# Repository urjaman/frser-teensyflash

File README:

Firmware for serprog on a Teensy 3.1,
supports my hardware (see hardware/)
with LPC,FWH and SPI.

You'll need to modify the Makefile
to point to your teensy toolchain,
assumed to be still inside
arduino 1.6.5.

It might be possible to still
compile under cygwin on windows,
but this was only tested on linux.

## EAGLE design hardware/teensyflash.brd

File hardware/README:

There be the EAGLE files (.sch,.brd) here,
gerbers in the .zip.
And the board is also shared in oshpark:
https://oshpark.com/shared_projects/izukIxq8

It is actually a bit tricky to build,
but i managed it. Dont short the PLCC
pins to the pin holes and dont
push the pins through the holes,
just in the holes, because the PLCC
socket goes above them.

There's a more detailed assembly description at:
http://flashrom.org/Teensy_3.1_SPI_%2B_LPC/FWH_Flasher

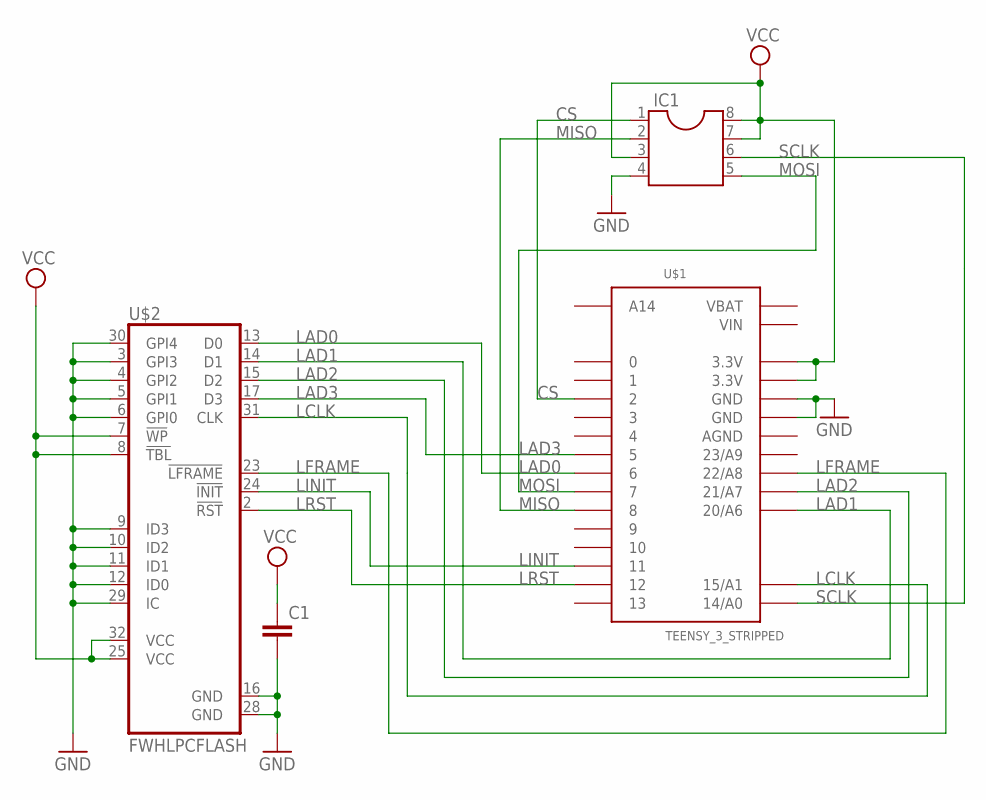
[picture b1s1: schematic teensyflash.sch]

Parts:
C1: C-EUC0805; C0805
IC1: DIL8; DIL08
U$1: TEENSY_3_STRIPPED
U$2: FWHLPCFLASH; PLCC32

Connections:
AGND: U$1.AGND
CS: IC1.1, U$1.2
GND: C1.2, IC1.4, U$1.GND, U$1.GND1 (GND), U$2.3 (GPI3), U$2.4 (GPI2), U$2.5 (GPI1), U$2.6 (GPI0), U$2.9 (ID3), U$2.10 (ID2), U$2.11 (ID1), U$2.12 (ID0), U$2.16 (GND), U$2.28 (GND), U$2.29 (IC), U$2.30 (GPI4)
LAD0: U$1.6, U$2.13 (D0)
LAD1: U$1.20/A6, U$2.14 (D1)
LAD2: U$1.21/A7, U$2.15 (D2)
LAD3: U$1.5, U$2.17 (D3)
LCLK: U$1.15/A1, U$2.31 (CLK)
LFRAME: U$1.22/A8, U$2.23 (!LFRAME)
LINIT: U$1.11, U$2.24 (!INIT)
LRST: U$1.12, U$2.2 (!RST)
MISO: IC1.2, U$1.8
MOSI: IC1.5, U$1.7
SCLK: IC1.6, U$1.14/A0
VBAT: U$1.VBAT
VCC: C1.1, IC1.3, IC1.7, IC1.8, U$1.3.3V, U$1.3.3V1 (3.3V), U$2.7 (!WP), U$2.8 (!TBL), U$2.25 (VCC), U$2.32 (VCC)
VIN: U$1.VIN

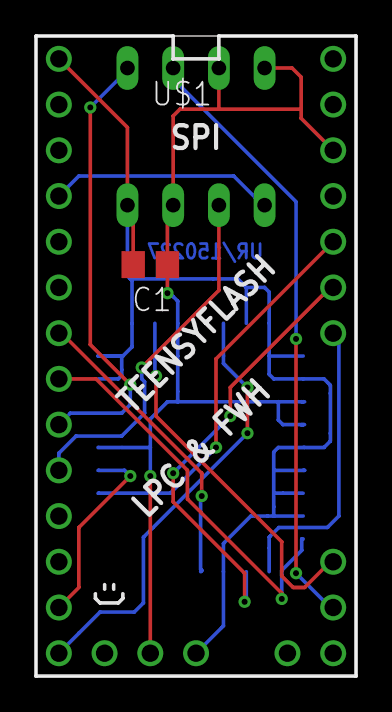
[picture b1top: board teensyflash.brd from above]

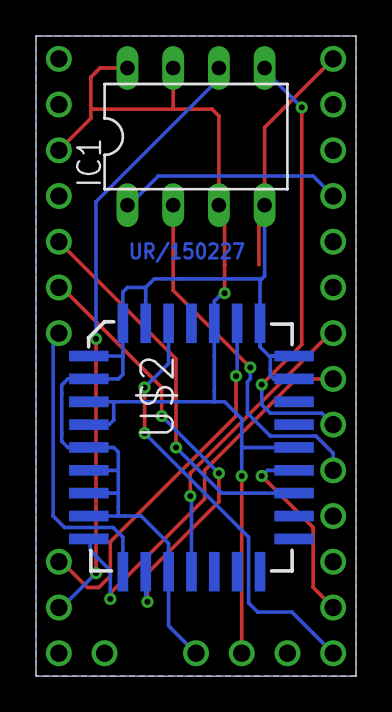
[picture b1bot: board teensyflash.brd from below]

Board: 2 copper layers, 17.8 x 35.6 mm, 4 parts (2 on the bottom side), 14 nets.

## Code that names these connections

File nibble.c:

/*
	This file was part of bbflash, now frser-teensyflash.
	Copyright (C) 2013, Hao Liu and Robert L. Thompson
	Copyright (C) 2013,2015 Urja Rannikko <urjaman@gmail.com>

	This program is free software: you can redistribute it and/or modify
	it under the terms of the GNU General Public License as published by
	the Free Software Foundation, either version 3 of the License, or
	(at your option) any later version.

	This program is distributed in the hope that it will be useful,
	but WITHOUT ANY WARRANTY; without even the implied warranty of
	MERCHANTABILITY or FITNESS FOR A PARTICULAR PURPOSE.  See the
	GNU General Public License for more details.

	You should have received a copy of the GNU General Public License
	along with this program.  If not, see <http://www.gnu.org/licenses/>.
*/
#include "main.h"
#include "nibble.h"


#define nopx() asm volatile("nop")

#define delay() nopx()

/* CLK: PC0
 * FRAME: PC1
 * INIT: PC6
 * RST: PC7
 * LAD0: PD4
 * LAD1: PD5
 * LAD2: PD6
 * LAD3: PD7
 */

void nibble_set_dir(uint8_t dir) {
	if (!dir) {
		GPIOD_PDDR &= ~(0xF0);
	} else {
		GPIOD_PDDR |= 0xF0;
	}
}

uint8_t nibble_read(void) {
	return (GPIOD_PDIR>>4)&0x0F;
}

static void nibble_write_hi(uint8_t data) {
	GPIOD_PDOR = (GPIOD_PDOR & ~0xF0) | (data & 0xF0);
}

void nibble_write(uint8_t data) {
	GPIOD_PDOR = (GPIOD_PDOR & ~0xF0) | (data << 4);
}

#define clock_low() do { GPIOC_PCOR = _BV(0); } while(0)
#define clock_high() do { GPIOC_PSOR = _BV(0); } while(0)

void clock_cycle(void) {
	clock_low();
	delay();
	clock_high();
}


bool nibble_init(void) {
	int i;

	GPIOC_PCOR = _BV(6); // INIT=0

	clock_high();

	GPIOC_PSOR = _BV(1); // FRAME

	nibble_set_dir(OUTPUT);
	nibble_write(0);

	for (i = 0; i < 24; i++)
		clock_cycle();
	GPIOC_PSOR = _BV(6); // INIT=1
	for (i = 0; i < 42; i++)
		clock_cycle();

	return true;
}

void nibble_cleanup(void) {
	GPIOC_PDDR &= ~(_BV(7) | _BV(6) | _BV(1) | _BV(0));
	nibble_set_dir(INPUT);
}

void clocked_nibble_write(uint8_t value) {
	clock_low();
	nibble_write(value);
	clock_high();
}

void clocked_nibble_write_hi(uint8_t value) {
	clock_low();
	nibble_write_hi(value);
	clock_high();
}

uint8_t clocked_nibble_read(void) {
	clock_cycle();
	delay();
#if F_CPU > 48000000
	delay();
#endif
	return nibble_read();
}

void nibble_start(uint8_t start) {
	GPIOC_PSOR = _BV(1); // FRAME=1
	nibble_set_dir(OUTPUT);
	clock_high();
	GPIOC_PCOR = _BV(1); // FRAME=0
	nibble_write(start);
	clock_cycle();
	GPIOC_PSOR = _BV(1); // FRAME=1
}


void nibble_hw_init(void) {
	/* Port Init */
	PORTC_PCR0 = PORT_PCR_MUX(1) | PORT_PCR_DSE | PORT_PCR_PE | PORT_PCR_PS;
	PORTC_PCR1 = PORT_PCR_MUX(1) | PORT_PCR_DSE | PORT_PCR_PE | PORT_PCR_PS;
	PORTC_PCR6 = PORT_PCR_MUX(1) | PORT_PCR_DSE | PORT_PCR_PE | PORT_PCR_PS;
	PORTC_PCR7 = PORT_PCR_MUX(1) | PORT_PCR_DSE | PORT_PCR_PE | PORT_PCR_PS;

	PORTD_PCR4 = PORT_PCR_MUX(1) | PORT_PCR_DSE | PORT_PCR_PE | PORT_PCR_PS;
	PORTD_PCR5 = PORT_PCR_MUX(1) | PORT_PCR_DSE | PORT_PCR_PE | PORT_PCR_PS;
	PORTD_PCR6 = PORT_PCR_MUX(1) | PORT_PCR_DSE | PORT_PCR_PE | PORT_PCR_PS;
	PORTD_PCR7 = PORT_PCR_MUX(1) | PORT_PCR_DSE | PORT_PCR_PE | PORT_PCR_PS;

	GPIOC_PDDR |= _BV(7) | _BV(6) | _BV(1) | _BV(0);
	GPIOC_PSOR = _BV(7) | _BV(6) | _BV(1) | _BV(0);
	GPIOD_PDDR &= ~(0xF0);
	GPIOD_PSOR = 0xF0;

	/* Kick reset here so lpc/fwh.c doesnt need to know about how it is controlled. */
	GPIOC_PCOR = _BV(7); // RST=0
	_delay_us(1);
	GPIOC_PSOR = _BV(7); // RST=1
}

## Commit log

2015-03-04 Teensy 3.1 C Makefile base (in cygwin) ... ugh...
2015-03-06 Add support for linux stuff, make blink not kill you.
2015-04-24 start work on making the makefile compatible with libfrser and include the module
2015-04-24 frakking frak this stuff is crappy...
2015-04-25 commit to celebrate first communication with flashrom
    no hardware code implemented yet (just nop stubs) (except usb serial obvs)
2015-04-26 spi: working, also configure the fake sizes of stuff to be saner
2015-04-28 first nibble support that surprisingly started working o.O
2015-04-28 dynamic bustypes... thought it'd be nice (supposed to help me debug...)
2015-04-28 update libfrser
2015-05-02 drop LTO, it makes problems (with the USB serial)... :'(
    Note: I want LTO, this is really annoying...
    darn not-invented-here USB stack
2015-05-02 This is kinda stupid unused delay ns implementation, but since i did it...
2015-05-02 Fix license headers etc
2015-05-02 Implement RX buffering in uart.c
    To be on the safe side so there is always space somewhere
    (even during TX) for the amount of RX buffering we claim to have.
2015-05-02 Use libfrser provided hooks for busy led and uart tx
2015-05-02 make mybool use ints on the teensy, makes more sense on a 32bit mcu
2015-05-02 switch nibble delay back to a nop (it works)
    There is the mystery that the first time the LPC didnt work
    and then suddenly it did, i havent been able to figure out that.
2015-05-02 nibble: get rid of some unnecessary delays
    I left the one in clock_cycle ... but even that shouldnt be needed
    At 48Mhz the teensy should be capable of max 24Mhz thus always <33Mhz
    The delay in the readback might be needed.
2015-05-02 Add files for the hardware...
2015-05-02 Make the name more descriptive
2015-05-02 Add a README with something useful...
2015-05-02 cleanup Makefiles
2015-05-02 bring back LTO on only the frser side of the codebase
2015-05-02 Get rid of HW Serial stuff
    You know, we can pull the code (and make it better) from the
    history if we need the functionality later.
    But compiling the repetitive 3*same thing code that isnt used
    is just meh.
2015-05-02 more cleanup
2015-05-02 little more cleanup
2015-05-03 Make the pin ISRs use CLZ, it makes them smaller
    Note: this is untested, i have no pin ISRs in use...
2015-05-03 Move all of code to SRAM, and remove startup early hook
    Hook removed because when .text was moved to SRAM that
    was a jump to .text before the flash->SRAM copy and *poof*
2015-05-31 nibble: Support for overclocking to 96Mhz - requires one more cycle in the read
2015-07-16 more unused stuff out the door
2015-07-16 remove the late hook too since unused
2015-07-16 unused redirector header out the door
2015-07-16 uart: Trying out sleeping a bit...
2015-07-16 default to overclocked 96Mhz
    seems to work fine and be used by lots of ppl, so ...
    drop to 48Mhz if you're scared, the bus speed is the same
    so shouldnt change SPI much - LPC needs CPU bit twiddling
    so this mostly for LPC.
    Warning: 72Mhz CPU makes for bad bus speed for SPI.
2015-07-16 We should have enough support for the pin state command, enable it.
    Now I think you should be able to ISP with the teensy 3.1.
    Somebody please test :)
2015-07-16 minimize veneers by splitting ResetHandler to have a RAM part at end
    this could be used to add a a late hook somewhere again if needed
    too... maybe even move the RAM copy earlier and such
2015-07-16 remove the (kinda pseudo-)EEPROM support, frser doesnt need eeprom
2015-07-16 remove unused math_helper stuff
    why? unused.
2015-07-16 remove avr_emulation.cpp, stub the .h, remove SPIFIFO.h
    I'm still thankful for the emulation code existing :),
    just not anymore as i dont need it anymore.
2015-07-16 WMath: say bye bye
2015-07-16 WString: byebye
2015-07-18 Make yield.cpp (empty hook) be yield.c
    Now we have no more cpp components, so next we can get
    rid of the last bits of cpp support (obviously recoverable from
    history).
2015-07-18 get rid of the cpp new operator support bits in lib
2015-07-22 Remove C++-only stuff from the support lib
2015-07-22 Use new libfrser
2015-07-22 Update toolchain used by default to Teensyduino 1.24 / Arduino-1.6.5
    Also update usage of teensy_loader_cli to use the new soft reboot flag
2015-07-26 Update also the arduino version named in the README...
2015-07-28 Remove unused stuff pass n
2015-07-28 It has arduino in the name, so i'd like to delete it asap, but for now... ;P
2015-07-28 Link the new page at flashrom wiki in the hardware readme
